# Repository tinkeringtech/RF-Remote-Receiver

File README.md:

# ScoutMakes RF Remote Receiver Breakout

A compact, beginner-friendly breakout that adds a **4-button 315 MHz wireless remote** to any microcontroller project. A 315 MHz 4-channel receiver module decodes the key fob. An **NXP PCA9536** I/O expander then puts all four buttons on the **I2C bus at address `0x41`**, so the whole remote takes just two wires over Qwiic / STEMMA QT. If you'd rather skip I2C, you can route the four channel outputs straight to four GPIO pins.

The fob comes pre-paired, so it works out of the box. You don't need Bluetooth, Wi-Fi or a pairing app.

## Where to Buy

Coming soon to our distributor partners. See the [product page](https://scoutmakes.com/products/rf-remote-receiver/) for updates, or [contact us](https://scoutmakes.com/contact) with questions.

## Use Cases

Remote-trigger a robot, toggle lights or relays, start and stop animations, open a prop door, or give a wearable a hidden "mode" button. It works anywhere you want a wireless button without building an app or a Bluetooth stack.

## Images

<!-- Replace with product photos and demo video -->
j

## Features

- **4-button 315 MHz key fob included**, pre-paired to the receiver
- **I2C via NXP PCA9536** at address `0x41`: all four buttons over two wires
- **Qwiic / STEMMA QT connector** for plug-and-play, solderless wiring
- **Direct GPIO option**: wire the four channel outputs to four pins if you don't want I2C
- **3.3 V to 5 V operation**
- **2.54 mm (0.1") header** for breadboards (5-pin header included)
- **CircuitPython ready**, and also works from MicroPython, Arduino or anything that speaks I2C
- **OSHWA certified** open-source hardware
- [NXP PCA9536 product page](https://www.nxp.com/part/PCA9536D)

## What's in the Box

- RF Remote Receiver breakout board
- 4-button 315 MHz remote control key fob (pre-paired)
- 5-pin 2.54 mm header

**Not included:** antenna and Qwiic / STEMMA QT cable.

## Compatibility

Works with Adafruit boards (QT Py, Feather, Metro), Raspberry Pi, Arduino, SparkFun Qwiic boards, and any microcontroller with 3.3 V or 5 V I2C or digital inputs.

## Pinout

> **TODO (verify against the schematic before publishing):** The pin order below is a placeholder.

| Pin | Function |
| --- | --- |
| VIN | 3.3 V – 5 V power |
| GND | Ground |
| SDA | I2C data (also on the Qwiic / STEMMA QT connector) |
| SCL | I2C clock (also on the Qwiic / STEMMA QT connector) |
| …   | … |

### PCA9536 Channel Mapping

The examples assume this mapping. Adjust `BUTTONS` in the code if the board differs.

| Fob button | Receiver channel | PCA9536 pin | Input register bit |
| --- | --- | --- | --- |
| A | D0 | IO0 | bit 0 (`0x01`) |
| B | D1 | IO1 | bit 1 (`0x02`) |
| C | D2 | IO2 | bit 2 (`0x04`) |
| D | D3 | IO3 | bit 3 (`0x08`) |

## Wiring

### I2C (recommended)

Plug a Qwiic / STEMMA QT cable between the breakout and your board. That's it. The board answers at `0x41`, so you can run `i2c.scan()` to confirm it's there.

### Direct GPIO

Wire VIN and GND, then connect the four channel outputs to four digital input pins. See `RF-Receiver-CircuitPython-GPIO-Test.py`.

## Example Code

| File | What it does |
| --- | --- |
| `RF-Receiver-CircuitPython-Test.py` | CircuitPython over I2C (PCA9536). Prints button presses and lights the NeoPixel a different colour per button. Written for the QT Py RP2040. No extra libraries needed beyond `neopixel`. |
| `RF-Receiver-CircuitPython-GPIO-Test.py` | CircuitPython reading the four channel outputs directly on A0–A3. |
| `RF-Receiver-Arduino-Test/RF-Receiver-Arduino-Test.ino` | Arduino over I2C using `Wire`. Prints press and release events to Serial. |

### CircuitPython Quick Start

1. Install CircuitPython on your board.
2. Copy `neopixel.mpy` from the [CircuitPython library bundle](https://circuitpython.org/libraries) into `CIRCUITPY/lib`.
3. Copy `RF-Receiver-CircuitPython-Test.py` to the board as `code.py`.
4. Open the serial console and press the fob buttons.

### Reading the PCA9536 from Any Platform

The PCA9536 is simple enough to drive with no library:

1. Write `0x0F` to register `0x03` (Configuration) to make IO0–IO3 inputs. This is the power-on default anyway.
2. Read register `0x00` (Input Port). Bits 0–3 hold the current state of channels D0–D3.

## A Note on Momentary vs Latching Outputs

315 MHz 4-channel receiver modules come in **momentary** versions, where an output is high only while the button is held, and **latching or toggle** versions, where each press flips the output. The examples report both press and release edges, so they work either way. Check which behaviour your board has before designing around it.

## A Note on the Antenna

No antenna is included. For usable range, solder a quarter-wave wire antenna to the ANT pad. At 315 MHz that's about **23.8 cm (9.4")** of solid-core wire, kept straight and away from ground planes. Without an antenna, range drops to a few centimetres.

## A Note on Frequency and Region

315 MHz is common for remotes in North America and parts of Asia. In the UK and EU, short-range devices generally use 433.92 MHz or 868 MHz instead. Check your local rules before using a 315 MHz transmitter outside the regions it's intended for.

## License

Hardware design files and documentation: [CC BY-SA 4.0](https://creativecommons.org/licenses/by-sa/4.0/). See `LICENSE`.
Example code: MIT, as noted in each file's SPDX header.

ScoutMakes™ is a brand of TinkeringTech LLC.

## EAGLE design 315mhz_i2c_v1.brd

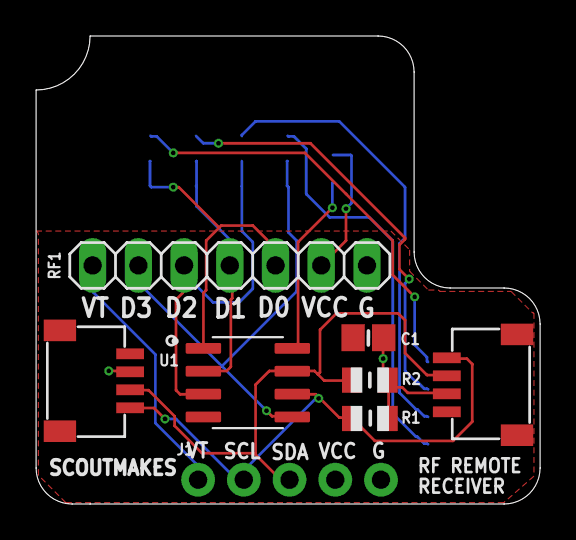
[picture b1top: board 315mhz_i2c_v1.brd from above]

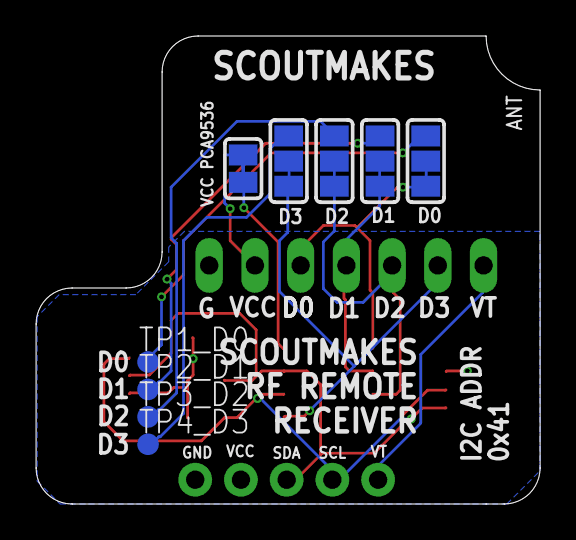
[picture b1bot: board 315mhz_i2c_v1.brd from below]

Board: 2 copper layers, 28.0 x 26.0 mm, 17 parts (9 on the bottom side), 14 nets.

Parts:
C1: 0.1uF; C0805
CONN3, CONN4: STEMMA_I2C_QT; JST_SH4
HP0, HP1, HP2, HP3: SOLDERJUMPER_2WAY_OPEN_NOPASTE
J1: 1X05_NO_SILK
JPVCC: SOLDERJUMPER_CLOSEDWIRE
R1, R2: 10K; R0805
RF1: MODULE; 1X07
TP1_D0, TP2_D1, TP3_D2, TP4_D3: TPTP12R; TP12R
U1: PCA9536D; SOIC127P599X175-8N

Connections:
D0: HP0.2, HP0.3, RF1.5, U1.1
D1: HP1.2, HP1.3, RF1.4, U1.2
D2: HP2.2, HP2.3, RF1.3, U1.3
D3: HP3.2, HP3.3, RF1.2, U1.5
GND: C1.2, CONN3.1, CONN3.MT1, CONN3.MT2, CONN4.1, CONN4.MT1, CONN4.MT2, J1.5, RF1.7, U1.4
unnamed: HP0.1, TP1_D0.TP
unnamed: HP1.1, TP2_D1.TP
unnamed: HP2.1, TP3_D2.TP
unnamed: HP3.1, TP4_D3.TP
SCL: CONN3.4, CONN4.4, J1.2, R1.1, U1.6
SDA: CONN3.3, CONN4.3, J1.3, R2.1, U1.7
VCC: C1.1, CONN3.2, CONN4.2, J1.4, JPVCC.1, R1.2, R2.2, RF1.6
VCCPCA: JPVCC.2, U1.8
VT: J1.1, RF1.1

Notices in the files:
parts and their libraries:
microbuilder: This work is placed in the public domain, and may be freely used for commercial and non-commercial work with the following conditions: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
SparkFun-Connectors: Licensing: Creative Commons ShareAlike 4.0 International - https://creativecommons.org/licenses/by-sa/4.0
